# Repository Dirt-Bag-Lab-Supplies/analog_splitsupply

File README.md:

# analog_splitsupply
Mixed buck + inverter and LDOs for adjustable split supply

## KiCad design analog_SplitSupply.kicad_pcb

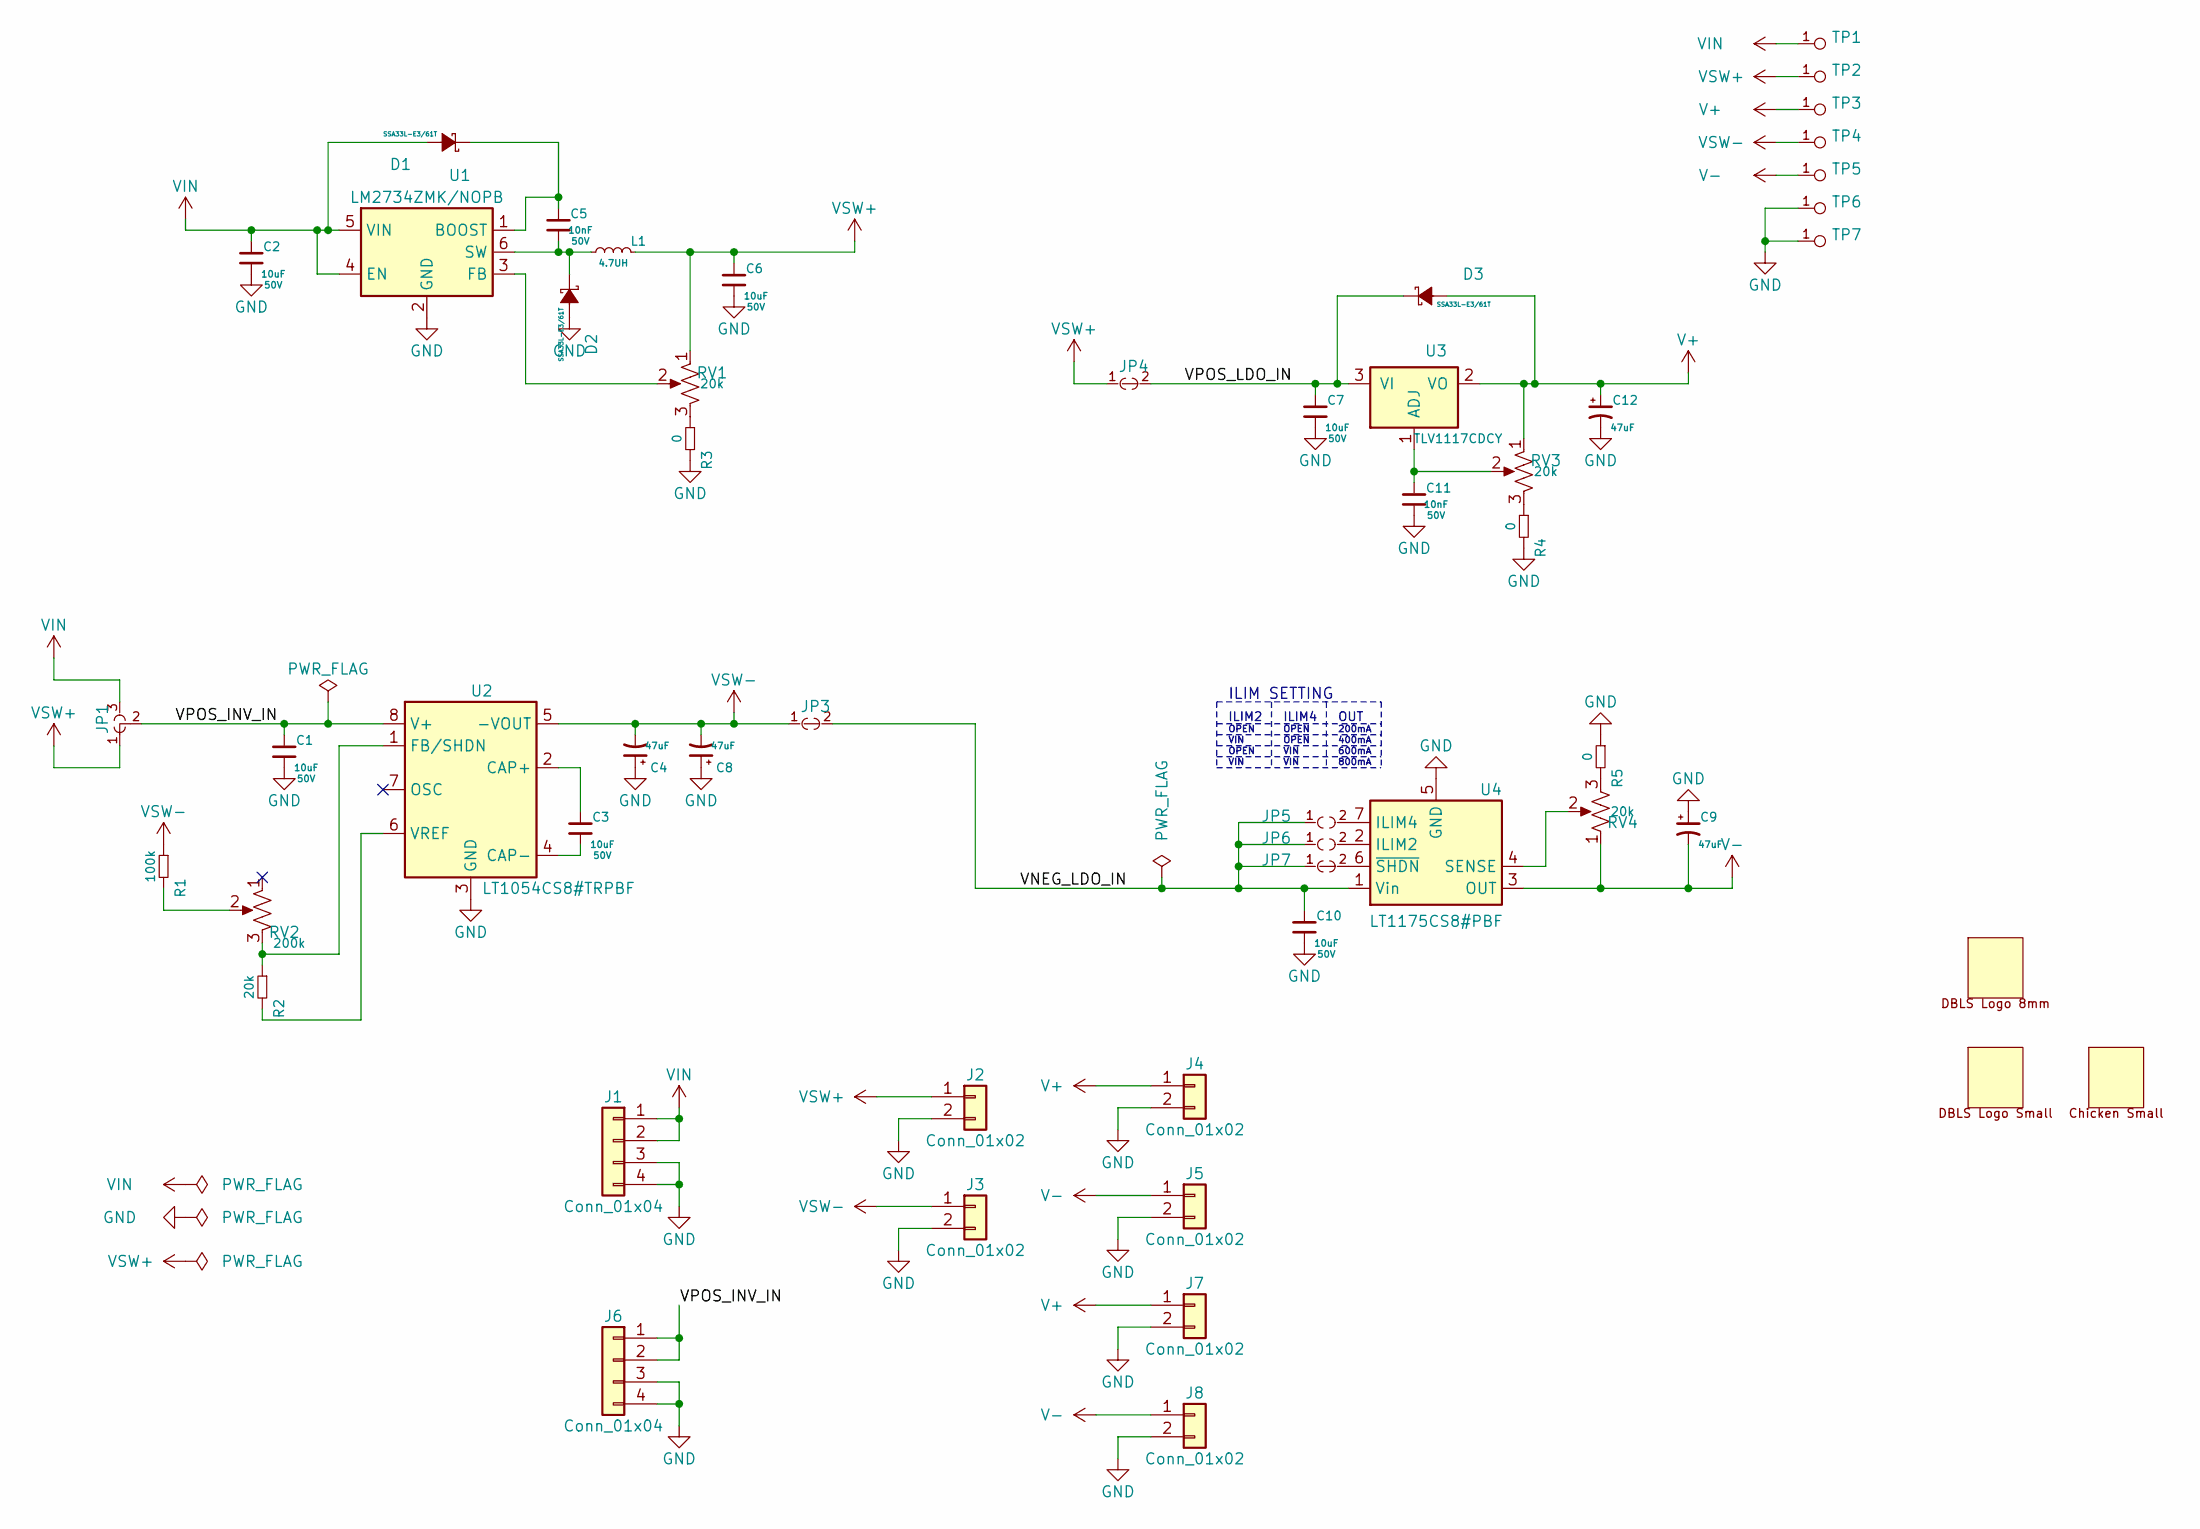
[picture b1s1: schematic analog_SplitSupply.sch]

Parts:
C1, C2, C3, C6, C7, C10: MURATA_GRT31CR61H106KE01L; C_1206; voltage 50V; mfg_pn GRT31CR61H106KE01L
C4, C8, C9, C12: KEMET_T495X476K035ATE200; CP_Tantalum_Case-X_EIA-7343-43_Reflow; mfg_pn T495X476K035ATE200
C5, C11: KEMET_C0603C103K5RAL7867; C_0603; voltage 50V; mfg_pn C0603C103K5RAL7867
D1, D2, D3: VISHAY_SSA33L-E3_61T; D_SMA; mfg_pn SSA33L-E3/61T
J1, J6: Conn_01x04; Pin_Header_Straight_1x04_Pitch2.54mm
J2, J3, J4, J5, J7, J8: Conn_01x02; Pin_Header_Straight_1x02_Pitch2.54mm
JP1: PAD_JUMPER_3PIN_12_NC_BY_TRACE
JP3, JP4, JP7: PAD_JUMPER_2PIN_NC_BY_TRACE
JP5, JP6: PAD_JUMPER_2PIN_NO; PAD_JUMPER_2PIN_NO_0603
L1: TDK_TFM322512ALVA4R7MTAA; L_1210; mfg_pn TFM322512ALVA4R7MTAA
LOGO1: DBLS_van_logo_small_v1; van_logo_small
LOGO2: DBLS_Chicken_Small; Rooster_4mmx4mm
LOGO3: DBLS_van_logo_8mmX6mm; van_logo_8mmX6mm
R1: VISHAYDALE_RCA0603100KFKEAHP; R_0603; mfg_pn RCA0603100KFKEAHP
R2: VISHAYDALE_CRCW060320K0FKTA; R_0603; mfg_pn CRCW060320K0FKTA
R3, R4, R5: YAGEO_RC0603JR-070RL; R_0603; mfg_pn RC0603JR-070RL
RV1, RV3, RV4: BOURNS_PV37W203C01B00; Potentiometer_Trimmer_Bourns_3299Y; mfg_pn PV37W203C01B00
RV2: BOURNS_PV37W204C01B00; Potentiometer_Trimmer_Bourns_3299Y; mfg_pn PV37W204C01B00
TP1, TP2, TP3, TP4, TP5, TP6, TP7: DBLS_TESTPOINT_NORMAL; DBLS_Testpoint_Normal
U1: TI_LM2734ZMK_NOPB; SOT-23-6; mfg_pn LM2734ZMK/NOPB
U2: AD_LT1054CS8#TRPBF; SOIC-8-N; mfg_pn LT1054CS8#TRPBF
U3: TI_TLV1117CDCY; SOT-223-3Lead_TabPin2; mfg_pn TLV1117CDCY
U4: AD_LT1175CS8#PBF; SOIC-8-N; mfg_pn LT1175CS8#PBF

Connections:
/VNEG_LDO_IN: C10.1, JP3.2, JP5.1, JP6.1, JP7.1, U4.1 (Vin), U4.8 (Vin)
/VPOS_INV_IN: C1.1, J6.1, J6.2, JP1.2, U2.8 (V+)
/VPOS_LDO_IN: C7.1, D3.1 (K), JP4.2, U3.3 (VI)
GND: C1.2, C2.2, C4.1, C6.2, C7.2, C8.1, C9.1, C10.2, C11.2, C12.2, D2.2 (A), J1.3, J1.4, J2.2, J3.2, J4.2, J5.2, J6.3, J6.4, J7.2, J8.2, R3.2, R4.2, R5.1, TP6.1, TP7.1, U1.2 (GND), U2.3 (GND), U4.5 (GND)
unnamed: C3.1, U2.2 (CAP+)
unnamed: C3.2, U2.4 (CAP-)
unnamed: C5.1, D1.1 (K), U1.1 (BOOST)
unnamed: C5.2, D2.1 (K), L1.1, U1.6 (SW)
unnamed: C11.1, RV3.2, U3.1 (ADJ)
unnamed: JP5.2, U4.7 (ILIM4)
unnamed: JP6.2, U4.2 (ILIM2)
unnamed: JP7.2, U4.6 (~SHDN)
unnamed: R1.2, RV2.2
unnamed: R2.1, RV2.3, U2.1 (FB/SHDN)
unnamed: R2.2, U2.6 (VREF)
unnamed: R3.1, RV1.3
unnamed: R4.1, RV3.3
unnamed: R5.2, RV4.3
unnamed: RV1.2, U1.3 (FB)
unnamed: RV4.2, U4.4 (SENSE)
V+: C12.1, D3.2 (A), J4.1, J7.1, RV3.1, TP3.1, U3.2 (VO)
V-: C9.2, J5.1, J8.1, RV4.1, TP5.1, U4.3 (OUT)
VIN: C2.1, D1.2 (A), J1.1, J1.2, JP1.3, TP1.1, U1.4 (EN), U1.5 (VIN)
VSW+: C6.1, J2.1, JP1.1, JP4.1, L1.2, RV1.1, TP2.1
VSW-: C4.2, C8.2, J3.1, JP3.1, R1.1, TP4.1, U2.5 (-VOUT)

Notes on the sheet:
ILIM SETTING
ILIM2
ILIM4
OUT
OPEN
VIN
200mA
400mA
600mA
800mA

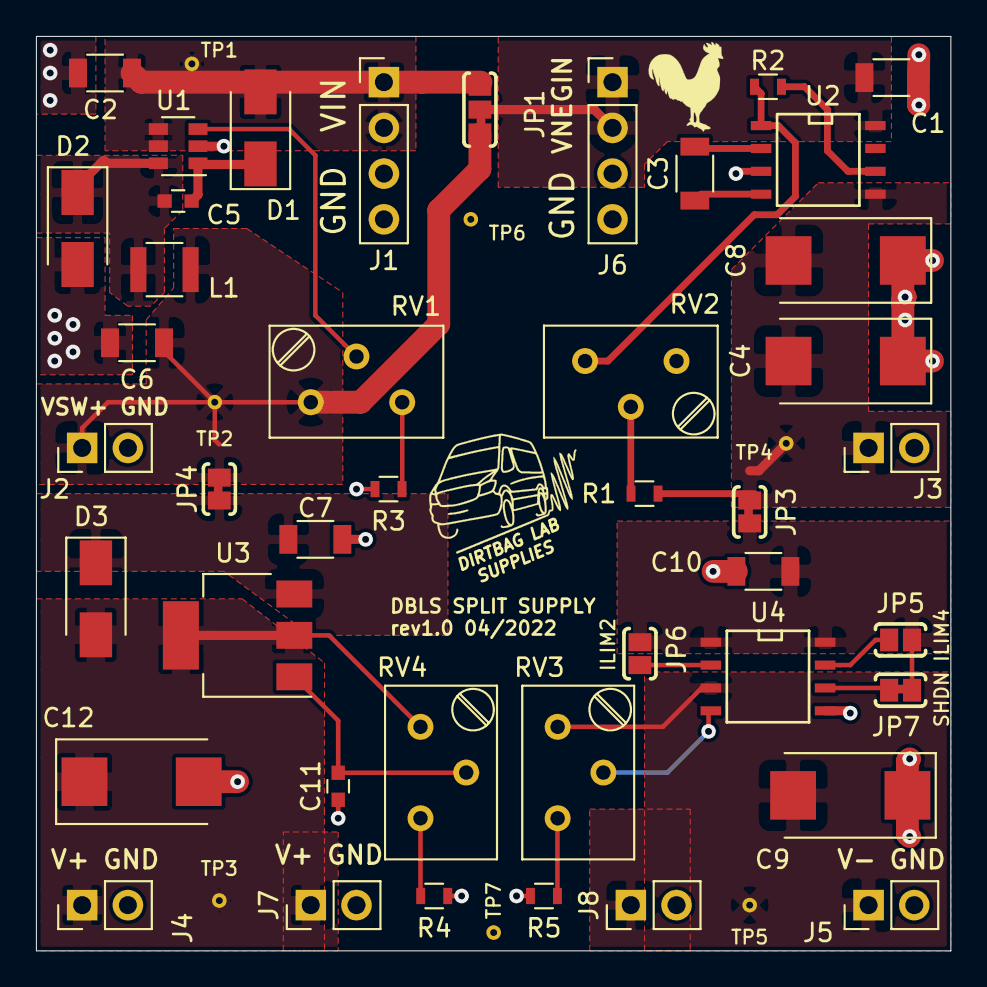
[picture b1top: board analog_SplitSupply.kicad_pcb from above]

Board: 2 copper layers, 50.8 x 50.8 mm, 53 parts (1 on the bottom side), 25 nets.

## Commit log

2022-03-25 first commit with schematic + minimal layout
2022-03-26 Updated schematic and prelim layout
2022-03-26 first route awaiting silkscreen cleanup
2022-03-26 cleaned up silkscreen
2022-03-26 updated schematic pdf
2022-04-18 Added logos, updated jumpers, and added second set of output headers.
